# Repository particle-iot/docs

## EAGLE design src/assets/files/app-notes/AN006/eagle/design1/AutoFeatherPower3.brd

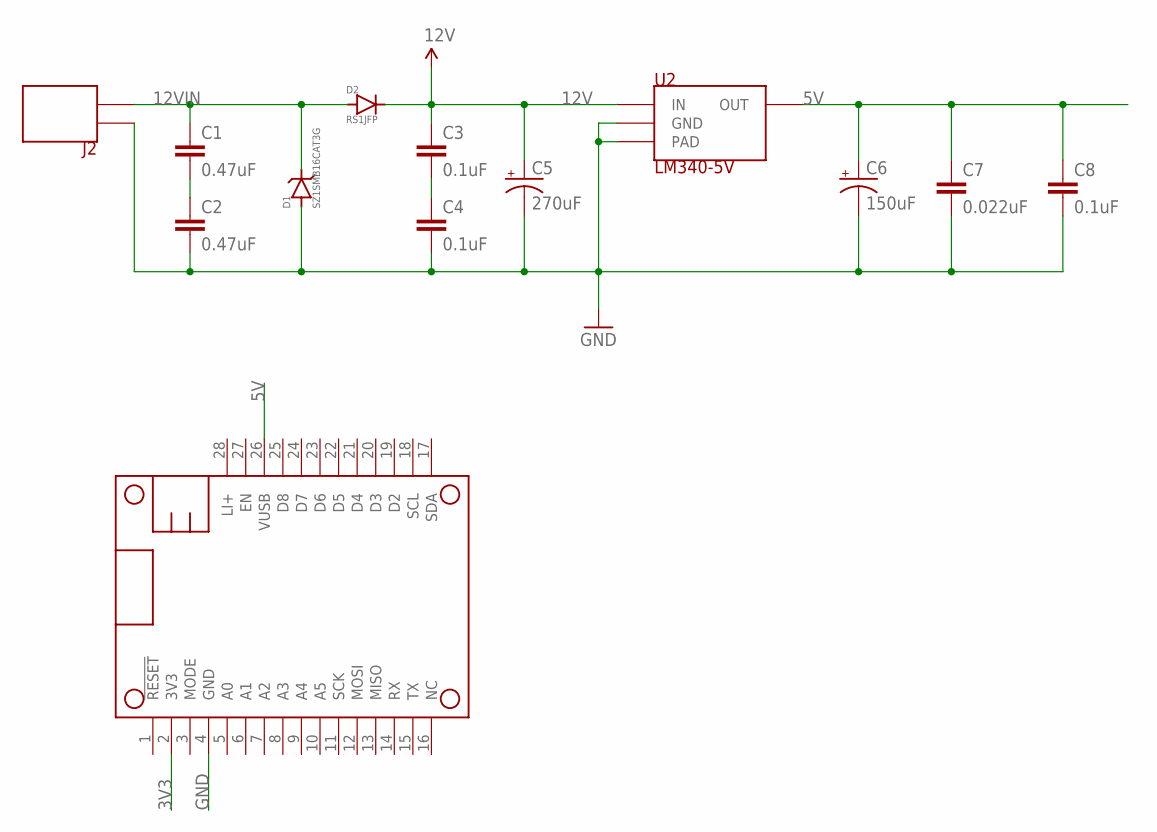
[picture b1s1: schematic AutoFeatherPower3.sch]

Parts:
C1, C2: 0.47uF; 0805
C3, C4, C8: 0.1uF; 0603-CAP
C5: 270uF; CAP-PANASONIC-FKS-V-F
C6: 150uF; CAP-PANASONIC-FKS-V-D
C7: 0.022uF; 0603-CAP
D1: SZ1SMB16CAT3G; SZ1SMB
D2: RS1JFP; SOD-123HE-ON
J2: TERMBLOCK-2X3.5MM
MS1: FEATHERWING_NODIM
U2: LM340-5V; TO-263-3-TI

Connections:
3V3: MS1.2 (3V3)
5V: C6.P+ (+), C7.1, C8.1, MS1.26 (VUSB), U2.3 (OUT)
12V: C3.1, C5.P+ (+), D2.1 (CATHODE), U2.1 (IN)
12VIN: C1.1, D1.C (CATHODE), D2.2 (ANODE), J2.2
GND: C2.2, C4.2, C5.P- (-), C6.P- (-), C7.2, C8.2, D1.A (ANODE), J2.1, MS1.4 (GND), U2.2 (GND), U2.PAD
unnamed: C1.2, C2.1
unnamed: C3.2, C4.1

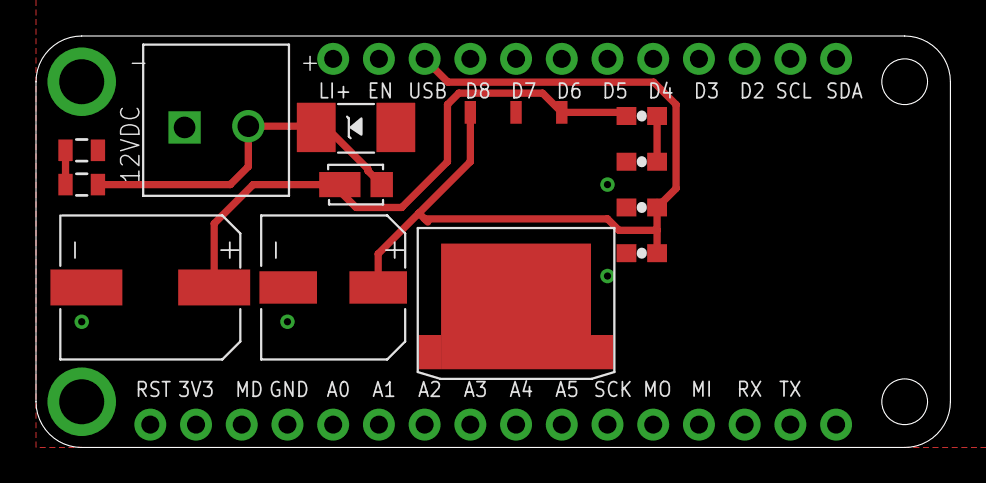
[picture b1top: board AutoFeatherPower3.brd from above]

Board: 2 copper layers, 50.8 x 22.9 mm, 13 parts (0 on the bottom side), 6 nets.

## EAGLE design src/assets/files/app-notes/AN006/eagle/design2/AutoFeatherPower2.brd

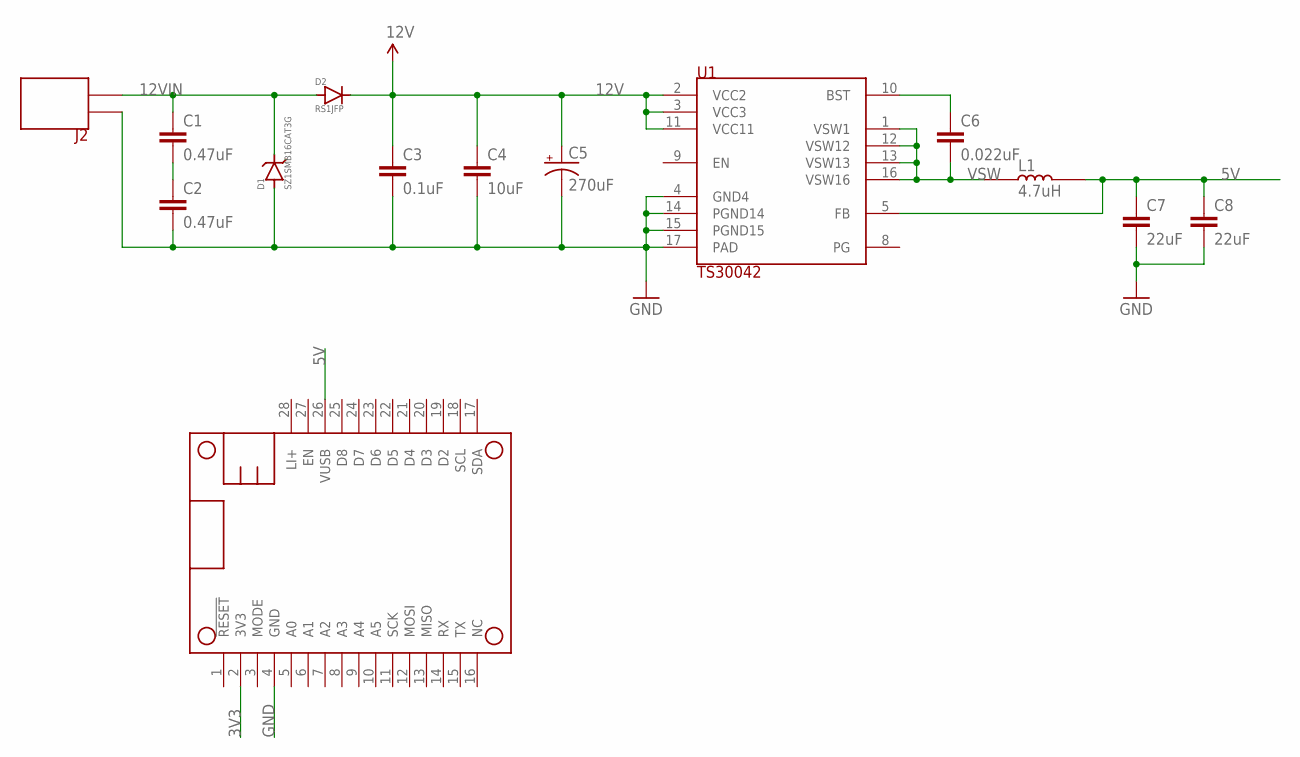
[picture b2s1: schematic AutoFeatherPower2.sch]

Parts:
C1, C2: 0.47uF; 0805
C3: 0.1uF; 0603-CAP
C4: 10uF; 0603-CAP
C5: 270uF; CAP-PANASONIC-FKS-V-F
C6: 0.022uF; 0603-CAP
C7, C8: 22uF; 0805
D1: SZ1SMB16CAT3G; SZ1SMB
D2: RS1JFP; SOD-123HE-ON
J2: TERMBLOCK-2X3.5MM
L1: 4.7uH; WURTH-744774047
MS1: FEATHERWING_NODIM
U1: TS30042; REG-TS30011

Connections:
3V3: MS1.2 (3V3)
5V: C7.1, C8.1, L1.2, MS1.26 (VUSB), U1.5 (FB)
12V: C3.1, C4.1, C5.P+ (+), D2.1 (CATHODE), U1.2 (VCC2), U1.3 (VCC3), U1.11 (VCC11)
12VIN: C1.1, D1.C (CATHODE), D2.2 (ANODE), J2.2
BST: C6.1, U1.10 (BST)
GND: C2.2, C3.2, C4.2, C5.P- (-), C7.2, C8.2, D1.A (ANODE), J2.1, MS1.4 (GND), U1.4 (GND4), U1.14 (PGND14), U1.15 (PGND15), U1.17 (PAD)
unnamed: C1.2, C2.1
VSW: C6.2, L1.1, U1.1 (VSW1), U1.12 (VSW12), U1.13 (VSW13), U1.16 (VSW16)

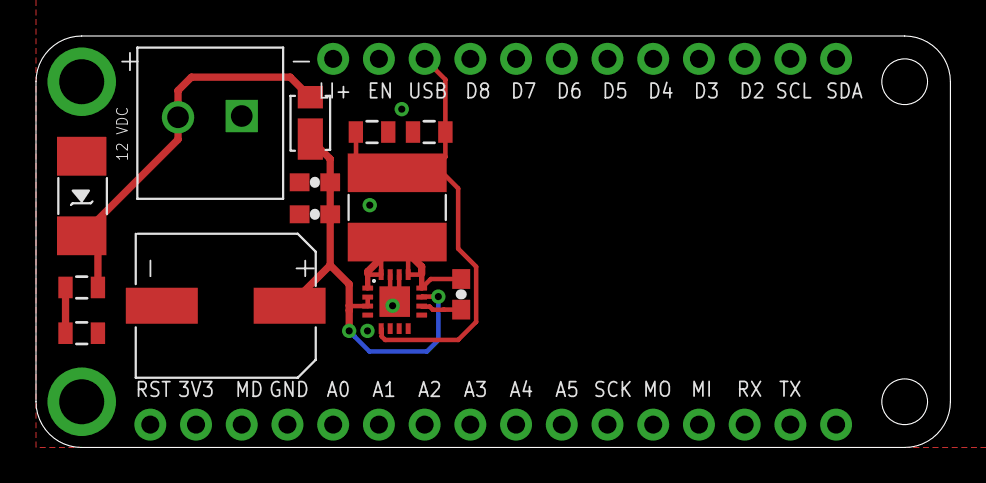
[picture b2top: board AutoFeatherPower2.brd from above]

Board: 2 copper layers, 50.8 x 22.9 mm, 14 parts (0 on the bottom side), 7 nets.

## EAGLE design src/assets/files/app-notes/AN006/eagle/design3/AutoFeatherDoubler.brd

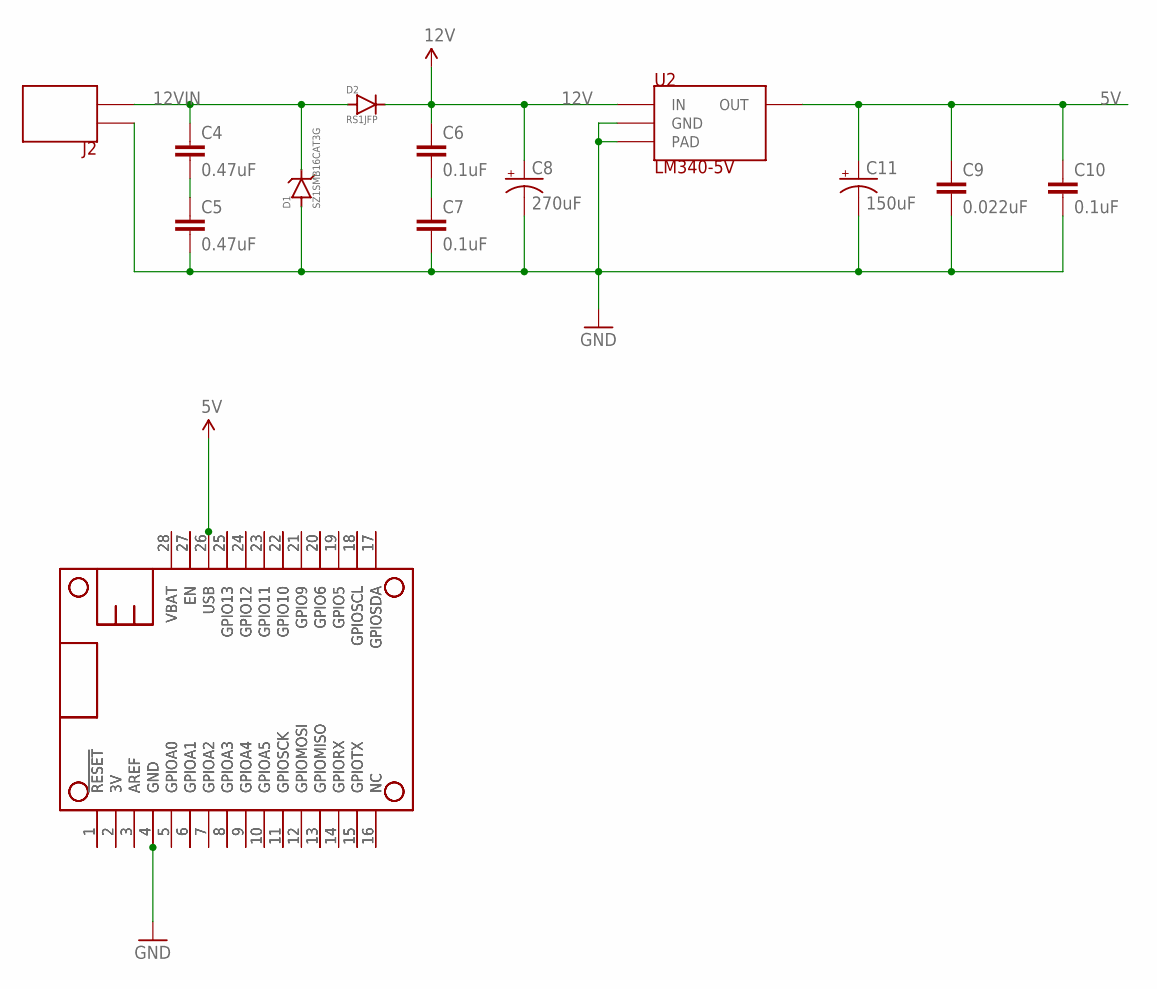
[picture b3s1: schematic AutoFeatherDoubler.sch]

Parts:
C4, C5: 0.47uF; 0805
C6, C7, C10: 0.1uF; 0603-CAP
C8: 270uF; CAP-270UF-25V-RADIAL-PTH
C9: 0.022uF; 0603-CAP
C11: 150uF; CAP-150UF-25V-RADIAL-PTH
D1: SZ1SMB16CAT3G; SZ1SMB
D2: RS1JFP; SOD-123HE-ON
J2: TERMBLOCK-2X3.5MM
MS1, MS2: FEATHERWING_NODIM; FEATHERWING_DIM
U2: LM340-5V; TO-263-3-TI

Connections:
3V3: MS1.2 (3V), MS2.2 (3V)
5V: C9.1, C10.1, C11.+, MS1.26 (USB), MS2.26 (USB), U2.3 (OUT)
12V: C6.1, C8.+, D2.1 (CATHODE), U2.1 (IN)
12VIN: C4.1, D1.C (CATHODE), D2.2 (ANODE), J2.2
A0: MS1.5 (GPIOA0), MS2.5 (GPIOA0)
A1: MS1.6 (GPIOA1), MS2.6 (GPIOA1)
A2: MS1.7 (GPIOA2), MS2.7 (GPIOA2)
A3: MS1.8 (GPIOA3), MS2.8 (GPIOA3)
A4: MS1.9 (GPIOA4), MS2.9 (GPIOA4)
A5: MS1.10 (GPIOA5), MS2.10 (GPIOA5)
D2: MS1.19 (GPIO5), MS2.19 (GPIO5)
D3: MS1.20 (GPIO6), MS2.20 (GPIO6)
D4: MS1.21 (GPIO9), MS2.21 (GPIO9)
D5: MS1.22 (GPIO10), MS2.22 (GPIO10)
D6: MS1.23 (GPIO11), MS2.23 (GPIO11)
D7: MS1.24 (GPIO12), MS2.24 (GPIO12)
D8: MS1.25 (GPIO13), MS2.25 (GPIO13)
EN: MS1.27 (EN), MS2.27 (EN)
GND: C5.2, C7.2, C8.-, C9.2, C10.2, C11.-, D1.A (ANODE), J2.1, MS1.4 (GND), MS2.4 (GND), U2.2 (GND), U2.PAD
MD: MS1.3 (AREF), MS2.3 (AREF)
MISO: MS1.13 (GPIOMISO), MS2.13 (GPIOMISO)
MOSI: MS1.12 (GPIOMOSI), MS2.12 (GPIOMOSI)
unnamed: C4.2, C5.1
unnamed: C6.2, C7.1
NC: MS1.16 (NC), MS2.16 (NC)
RESET: MS1.1 (!RESET), MS2.1 (!RESET)
RX: MS1.14 (GPIORX), MS2.14 (GPIORX)
SCK: MS1.11 (GPIOSCK), MS2.11 (GPIOSCK)
SCL: MS1.18 (GPIOSCL), MS2.18 (GPIOSCL)
SDA: MS1.17 (GPIOSDA), MS2.17 (GPIOSDA)
TX: MS1.15 (GPIOTX), MS2.15 (GPIOTX)
VBAT: MS1.28 (VBAT), MS2.28 (VBAT)

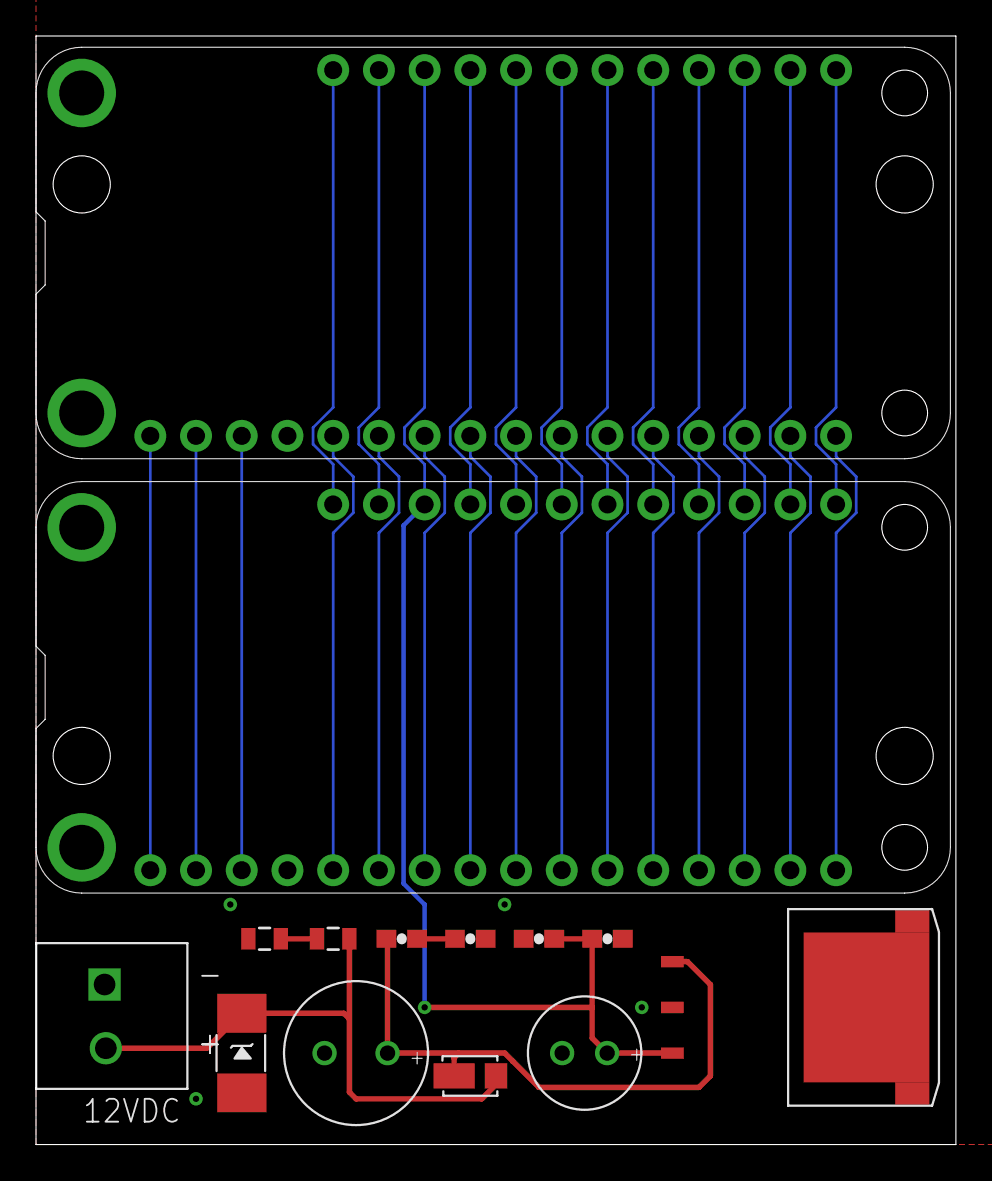
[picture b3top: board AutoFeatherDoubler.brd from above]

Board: 2 copper layers, 51.1 x 61.6 mm, 14 parts (0 on the bottom side), 32 nets.

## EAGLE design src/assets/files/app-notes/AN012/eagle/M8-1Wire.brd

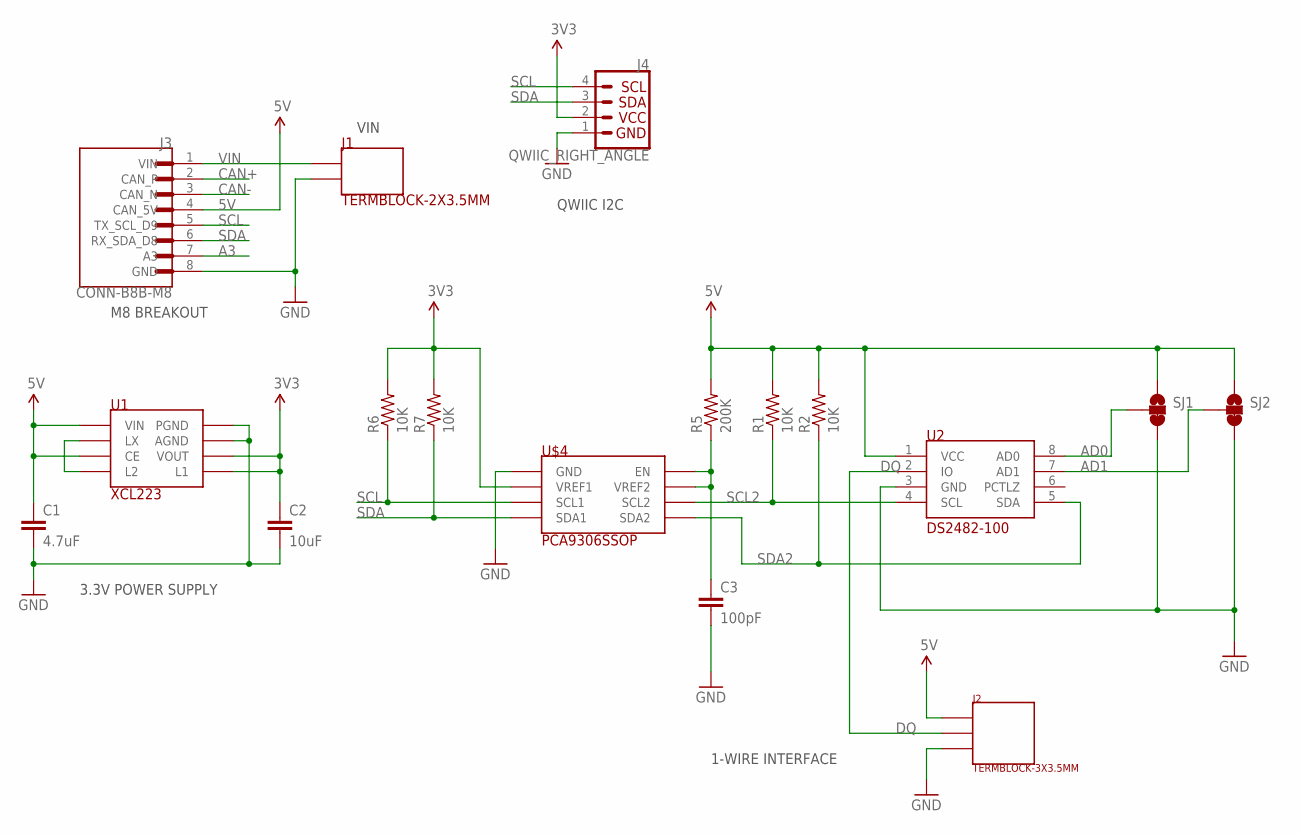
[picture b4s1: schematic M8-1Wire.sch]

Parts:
C1: 4.7uF; 0603-CAP
C2: 10uF; 0603-CAP
C3: 100pF; 0603-CAP
J1: TERMBLOCK-2X3.5MM
J2: TERMBLOCK-3X3.5MM
J3: CONN-B8B-M8; JST_B8B-PH-SM4-TB(LF)(SN)
J4: QWIIC_RIGHT_ANGLE; JST04_1MM_RA
R1, R2, R6, R7: 10K; 0603-RES
R5: 200K; 0603-RES
SJ1, SJ2: JUMPER-PAD-3-2OF3_NC_BY_TRACE_SMALL; PAD-JUMPER-3-2OF3_NC_BY_TRACE_NO_SILK
U1: XCL223; REG-XCL223-LESS-CREAM
U2: DS2482-100; 8-SOIC-MAXIM
U$4: PCA9306SSOP; 8-SSOP-TI

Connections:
3V3: C2.1, J4.2, R6.2, R7.2, U1.3 (VOUT), U1.7 (L1), U$4.2 (VREF1)
5V: C1.1, J2.1, J3.4 (CAN_5V), R1.2, R2.2, R5.2, SJ1.1, SJ2.1, U1.4 (CE), U1.6 (VIN), U2.1 (VCC)
A3: J3.7 (A3)
AD0: SJ1.2, U2.8 (AD0)
AD1: SJ2.2, U2.7 (AD1)
CAN+: J3.2 (CAN_P)
CAN-: J3.3 (CAN_N)
DQ: J2.2, U2.2 (IO)
GND: C1.2, C2.2, C3.2, J1.2, J2.3, J3.8 (GND), J4.1, SJ1.3, SJ2.3, U1.1 (PGND), U1.2 (AGND), U2.3 (GND), U$4.1 (GND)
LX: U1.5 (LX), U1.8 (L2)
SCL: J3.5 (TX_SCL_D9), J4.4, R6.1, U$4.3 (SCL1)
SCL2: R1.1, U2.4 (SCL), U$4.6 (SCL2)
SDA: J3.6 (RX_SDA_D8), J4.3, R7.1, U$4.4 (SDA1)
SDA2: R2.1, U2.5 (SDA), U$4.5 (SDA2)
VIN: J1.1, J3.1 (VIN)
VREF2_EN: C3.1, R5.1, U$4.7 (VREF2), U$4.8 (EN)

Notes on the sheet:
3.3V POWER SUPPLY
QWIIC I2C
M8 BREAKOUT
VIN
1-WIRE INTERFACE

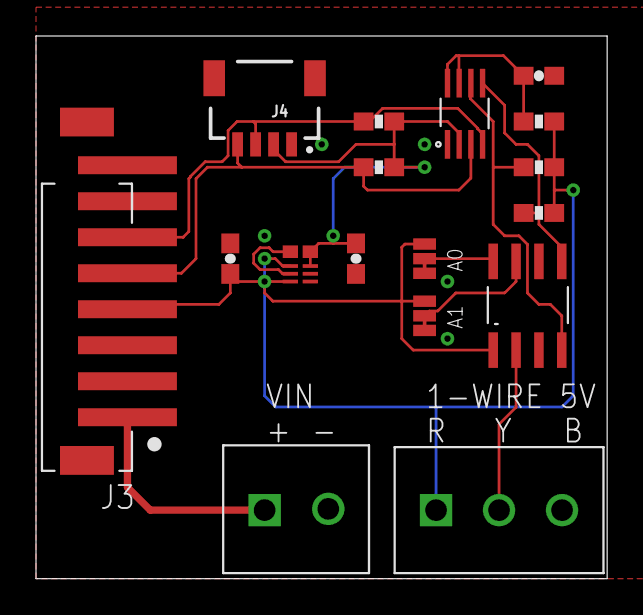
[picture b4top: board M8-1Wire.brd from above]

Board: 2 copper layers, 31.7 x 30.1 mm, 17 parts (0 on the bottom side), 13 nets.

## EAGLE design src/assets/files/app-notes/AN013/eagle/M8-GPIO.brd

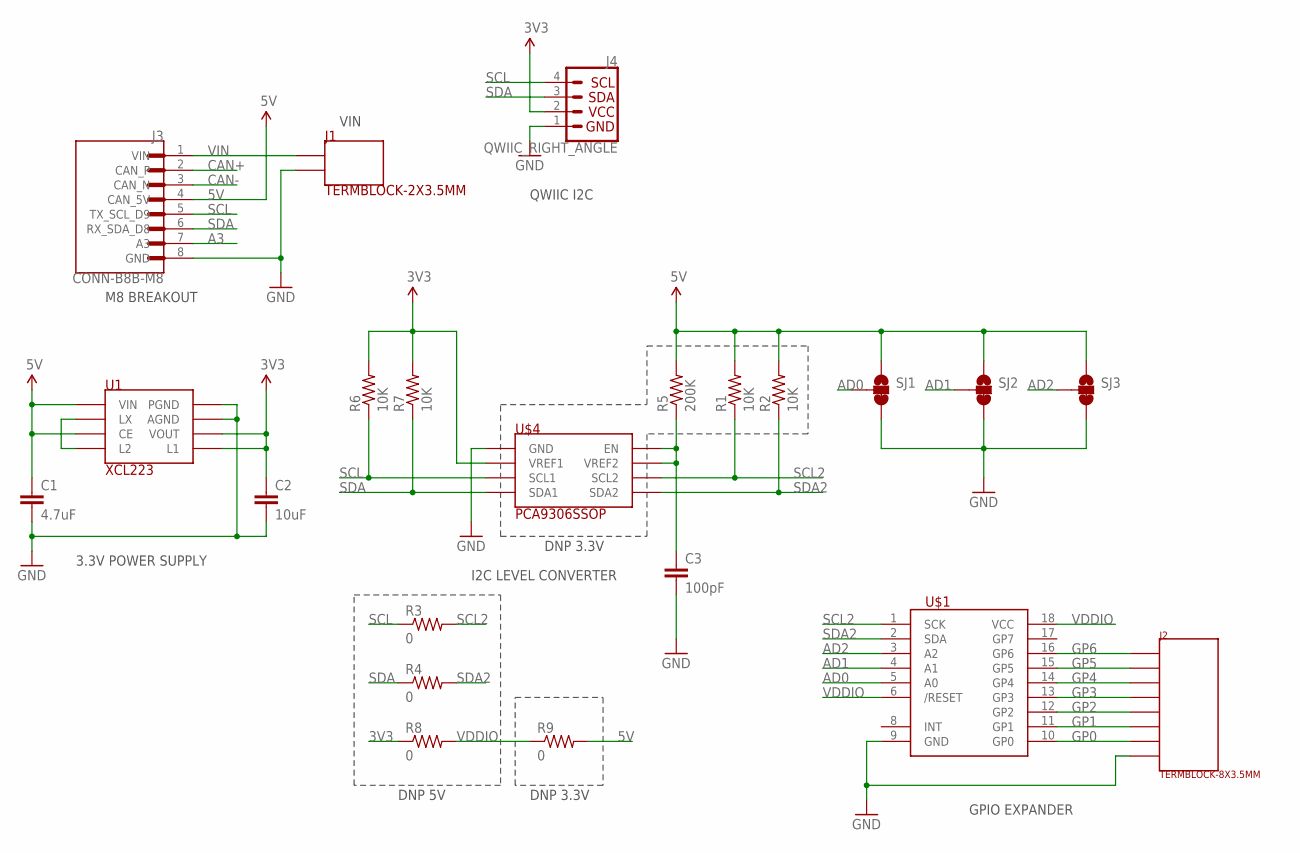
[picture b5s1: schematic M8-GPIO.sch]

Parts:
C1: 4.7uF; 0603-CAP
C2: 10uF; 0603-CAP
C3: 100pF; 0603-CAP
J1: TERMBLOCK-2X3.5MM
J2: TERMBLOCK-8X3.5MM
J3: CONN-B8B-M8; JST_B8B-PH-SM4-TB(LF)(SN)
J4: QWIIC_RIGHT_ANGLE; JST04_1MM_RA
R1, R2, R6, R7: 10K; 0603-RES
R3, R4, R8, R9: 0; 0603-RES
R5: 200K; 0603-RES
SJ1, SJ2, SJ3: JUMPER-PAD-3-2OF3_NC_BY_TRACE_SMALL; PAD-JUMPER-3-2OF3_NC_BY_TRACE_NO_SILK
U1: XCL223; REG-XCL223-LESS-CREAM
U$1: MCP23008; SOIC-18-W-MAXIM
U$4: PCA9306SSOP; 8-SSOP-TI

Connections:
3V3: C2.1, J4.2, R6.2, R7.2, R8.1, U1.3 (VOUT), U1.7 (L1), U$4.2 (VREF1)
5V: C1.1, J3.4 (CAN_5V), R1.2, R2.2, R5.2, R9.2, SJ1.1, SJ2.1, SJ3.1, U1.4 (CE), U1.6 (VIN)
A3: J3.7 (A3)
AD0: SJ1.2, U$1.5 (A0)
AD1: SJ2.2, U$1.4 (A1)
AD2: SJ3.2, U$1.3 (A2)
CAN+: J3.2 (CAN_P)
CAN-: J3.3 (CAN_N)
GND: C1.2, C2.2, C3.2, J1.2, J2.8, J3.8 (GND), J4.1, SJ1.3, SJ2.3, SJ3.3, U1.1 (PGND), U1.2 (AGND), U$1.9 (GND), U$4.1 (GND)
GP0: J2.7, U$1.10 (GP0)
GP1: J2.6, U$1.11 (GP1)
GP2: J2.5, U$1.12 (GP2)
GP3: J2.4, U$1.13 (GP3)
GP4: J2.3, U$1.14 (GP4)
GP5: J2.2, U$1.15 (GP5)
GP6: J2.1, U$1.16 (GP6)
LX: U1.5 (LX), U1.8 (L2)
SCL: J3.5 (TX_SCL_D9), J4.4, R3.1, R6.1, U$4.3 (SCL1)
SCL2: R1.1, R3.2, U$1.1 (SCK), U$4.6 (SCL2)
SDA: J3.6 (RX_SDA_D8), J4.3, R4.1, R7.1, U$4.4 (SDA1)
SDA2: R2.1, R4.2, U$1.2 (SDA), U$4.5 (SDA2)
VDDIO: R8.2, R9.1, U$1.6 (/RESET), U$1.18 (VCC)
VIN: J1.1, J3.1 (VIN)
VREF2_EN: C3.1, R5.1, U$4.7 (VREF2), U$4.8 (EN)

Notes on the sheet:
3.3V POWER SUPPLY
QWIIC I2C
M8 BREAKOUT
VIN
DNP 3.3V
DNP 5V
GPIO EXPANDER
I2C LEVEL CONVERTER

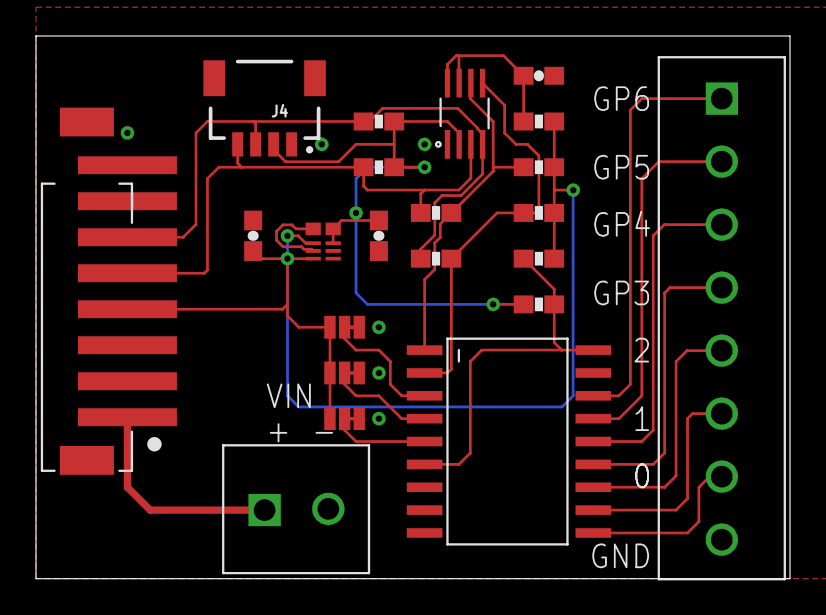
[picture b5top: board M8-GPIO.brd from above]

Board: 2 copper layers, 41.9 x 30.1 mm, 22 parts (0 on the bottom side), 21 nets.

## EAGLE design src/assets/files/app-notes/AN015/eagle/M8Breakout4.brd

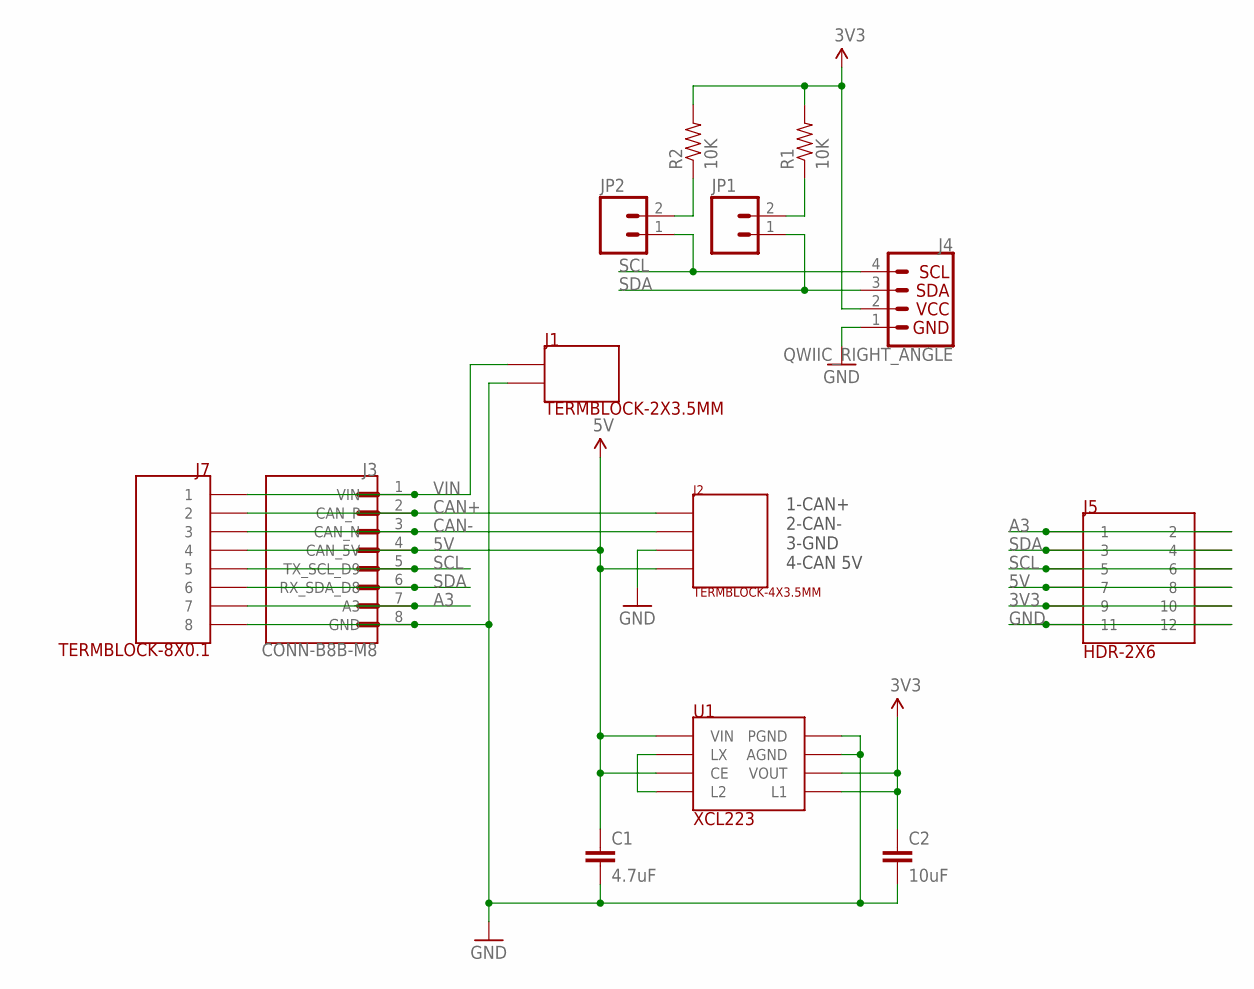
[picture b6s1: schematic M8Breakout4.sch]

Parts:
C1: 4.7uF; 0603-CAP
C2: 10uF; 0603-CAP
J1: TERMBLOCK-2X3.5MM
J2: TERMBLOCK-4X3.5MM
J3: CONN-B8B-M8; JST_B8B-PH-SM4-TB(LF)(SN)
J4: QWIIC_RIGHT_ANGLE; JST04_1MM_RA
J5: HDR-2X6; HDR-2X6-F-SMD-NO-HOLES
J7: TERMBLOCK-8X0.1
JP1, JP2: M02PTH; 1X02
R1, R2: 10K; 0603-RES
U1: XCL223; REG-XCL223-LESS-CREAM

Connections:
3V3: C2.1, J4.2, J5.9, J5.10, R1.2, R2.2, U1.3 (VOUT), U1.7 (L1)
5V: C1.1, J2.4, J3.4 (CAN_5V), J5.7, J5.8, J7.P$4 (4), U1.4 (CE), U1.6 (VIN)
A3: J3.7 (A3), J5.1, J5.2, J7.P$7 (7)
CAN+: J2.1, J3.2 (CAN_P), J7.P$2 (2)
CAN-: J2.2, J3.3 (CAN_N), J7.P$3 (3)
GND: C1.2, C2.2, J1.2, J2.3, J3.8 (GND), J4.1, J5.11, J5.12, J7.P$8 (8), U1.1 (PGND), U1.2 (AGND)
LX: U1.5 (LX), U1.8 (L2)
unnamed: JP2.2, R2.1
unnamed: JP1.2, R1.1
SCL: J3.5 (TX_SCL_D9), J4.4, J5.5, J5.6, J7.P$5 (5), JP2.1
SDA: J3.6 (RX_SDA_D8), J4.3, J5.3, J5.4, J7.P$6 (6), JP1.1
VIN: J1.1, J3.1 (VIN), J7.P$1 (1)

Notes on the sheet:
1-CAN+ 2-CAN- 3-GND 4-CAN 5V

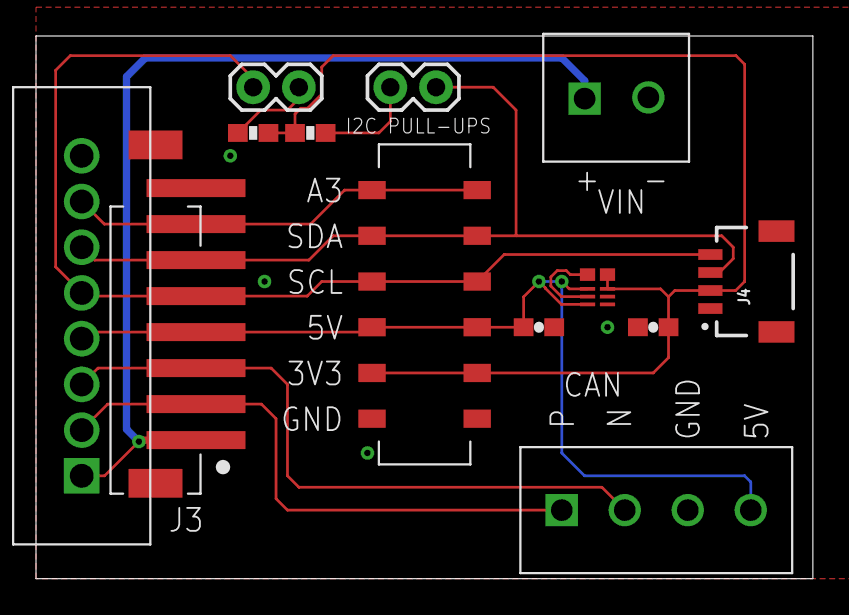
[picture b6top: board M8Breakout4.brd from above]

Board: 2 copper layers, 43.2 x 30.1 mm, 13 parts (0 on the bottom side), 12 nets.

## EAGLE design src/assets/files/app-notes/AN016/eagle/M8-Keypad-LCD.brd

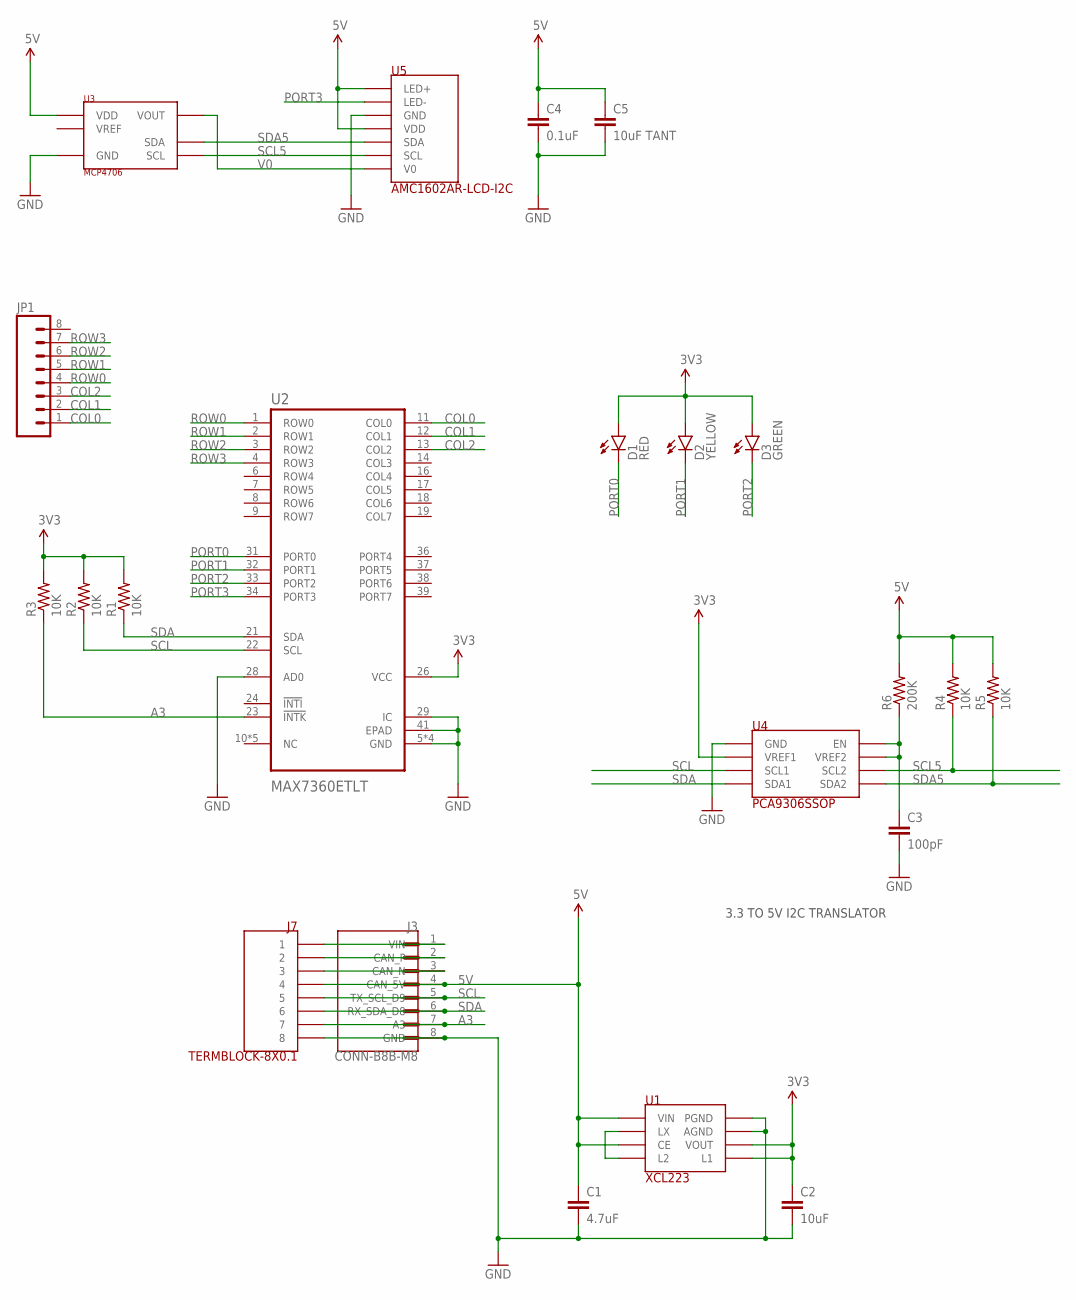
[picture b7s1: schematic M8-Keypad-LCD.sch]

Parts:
C1: 4.7uF; 0603-CAP
C2: 10uF; 0603-CAP
C3: 100pF; 0603-CAP
C4: 0.1uF; 0603-CAP
C5: 10uF TANT; 1206-KEMET
D1: RED; LED-0603
D2: YELLOW; LED-0603
D3: GREEN; LED-0603
J3: CONN-B8B-M8; JST_B8B-PH-SM4-TB(LF)(SN)
J7: TERMBLOCK-8X0.1
JP1: M08SILK_FEMALE_PTH; 1X08
R1, R2, R3, R4, R5: 10K; 0603-RES
R6: 200K; 0603-RES
U1: XCL223; REG-XCL223-LESS-CREAM
U2: MAX7360ETLT; QFN40P500X500X80-41N
U3: MCP4706; SOT-23-6-MICROCHIP
U4: PCA9306SSOP; 8-SSOP-TI
U5: AMC1602AR-LCD-I2C; AMC1602AR

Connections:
3V3: C2.1, D1.A, D2.A, D3.A, R1.2, R2.2, R3.2, U1.3 (VOUT), U1.7 (L1), U2.26 (VCC), U4.2 (VREF1)
5V: C1.1, C4.1, C5.1, J3.4 (CAN_5V), J7.P$4 (4), R4.2, R5.2, R6.2, U1.4 (CE), U1.6 (VIN), U3.3 (VDD), U5.1 (LED+), U5.4 (VDD)
A3: J3.7 (A3), J7.P$7 (7), R3.1, U2.23 (!INTK)
CAN+: J3.2 (CAN_P), J7.P$2 (2)
CAN-: J3.3 (CAN_N), J7.P$3 (3)
COL0: JP1.1, U2.11 (COL0)
COL1: JP1.2, U2.12 (COL1)
COL2: JP1.3, U2.13 (COL2)
GND: C1.2, C2.2, C3.2, C4.2, C5.2, J3.8 (GND), J7.P$8 (8), U1.1 (PGND), U1.2 (AGND), U2.5 (GND), U2.15 (GND), U2.25 (GND), U2.28 (AD0), U2.29 (IC), U2.35 (GND), U2.41 (EPAD), U3.2 (GND), U4.1 (GND), U5.3 (GND)
LX: U1.5 (LX), U1.8 (L2)
PORT0: D1.C, U2.31 (PORT0)
PORT1: D2.C, U2.32 (PORT1)
PORT2: D3.C, U2.33 (PORT2)
PORT3: U2.34 (PORT3), U5.2 (LED-)
ROW0: JP1.4, U2.1 (ROW0)
ROW1: JP1.5, U2.2 (ROW1)
ROW2: JP1.6, U2.3 (ROW2)
ROW3: JP1.7, U2.4 (ROW3)
SCL: J3.5 (TX_SCL_D9), J7.P$5 (5), R2.1, U2.22 (SCL), U4.3 (SCL1)
SCL5: R4.1, U3.5 (SCL), U4.6 (SCL2), U5.6 (SCL)
SDA: J3.6 (RX_SDA_D8), J7.P$6 (6), R1.1, U2.21 (SDA), U4.4 (SDA1)
SDA5: R5.1, U3.4 (SDA), U4.5 (SDA2), U5.5 (SDA)
V0: U3.1 (VOUT), U5.7 (V0)
VIN: J3.1 (VIN), J7.P$1 (1)
VREF2_EN: C3.1, R6.1, U4.7 (VREF2), U4.8 (EN)

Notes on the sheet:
3.3 TO 5V I2C TRANSLATOR

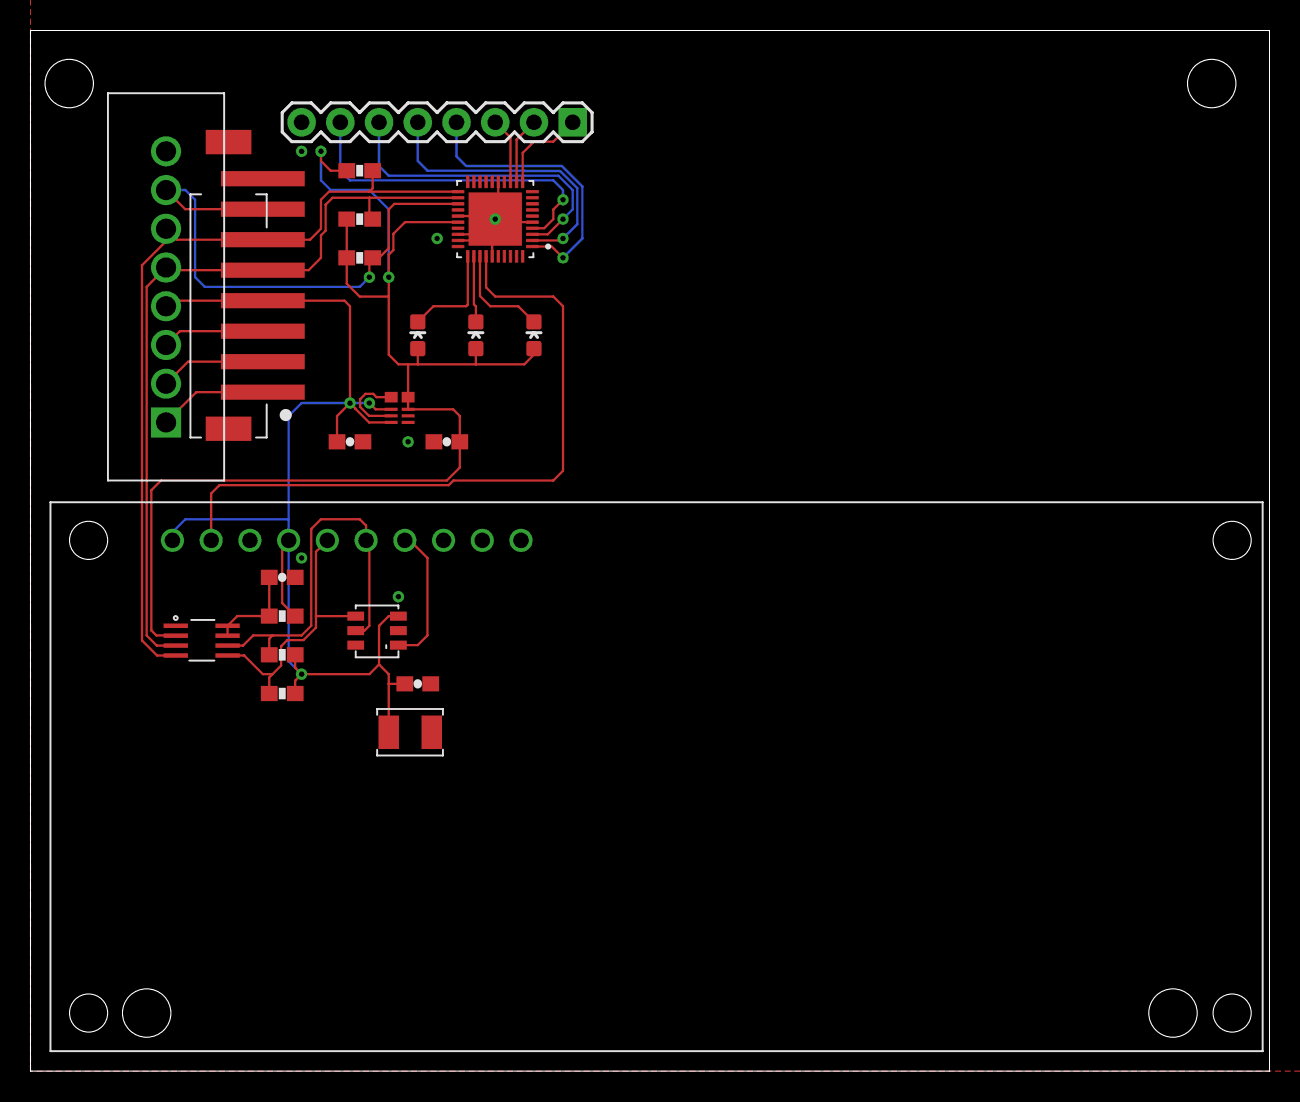
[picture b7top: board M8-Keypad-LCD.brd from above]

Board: 2 copper layers, 81.3 x 68.2 mm, 22 parts (0 on the bottom side), 25 nets.

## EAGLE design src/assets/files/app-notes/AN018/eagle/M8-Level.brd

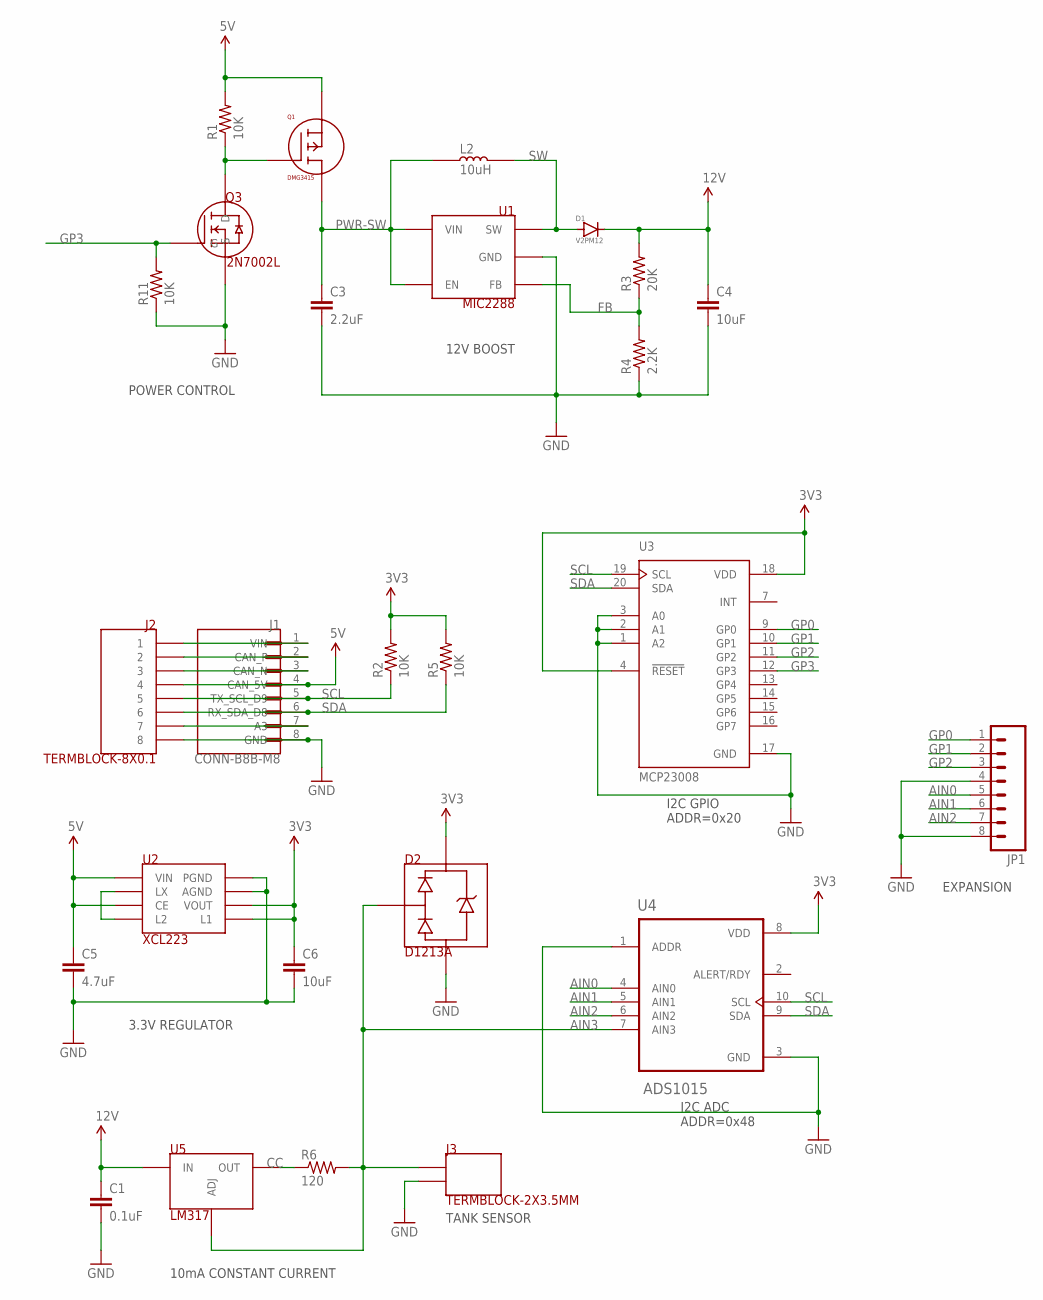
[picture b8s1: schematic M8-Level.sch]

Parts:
C1: 0.1uF; 0603-CAP
C3: 2.2uF; 0603-CAP
C4, C6: 10uF; 0603-CAP
C5: 4.7uF; 0603-CAP
D1: V2PM12; DO-219AD-VISHAY
D2: D1213A; DLP
J1: CONN-B8B-M8; JST_B8B-PH-SM4-TB(LF)(SN)
J2: TERMBLOCK-8X0.1
J3: TERMBLOCK-2X3.5MM
JP1: M08SILK_FEMALE_PTH; 1X08
L2: 10uH; BOURNS-INDUCTOR-3X3
Q1: DMG3415; 2N7002L
Q3: 2N7002L
R1, R2, R5, R11: 10K; 0603-RES
R3: 20K; 0603-RES
R4: 2.2K; 0603-RES
R6: 120; 0603-RES
U1: MIC2288; TSOT23-5-MICROCHIP
U2: XCL223; REG-XCL223-LESS-CREAM
U3: MCP23008; QFN21P50_400X400X100L40X24T270N
U4: ADS1015; SOP50P490X110-10N
U5: LM317; 8-SOIC-ON751

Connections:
3V3: C6.1, D2.VCC, R2.2, R5.2, U2.3 (VOUT), U2.7 (L1), U3.4 (!RESET), U3.18 (VDD), U4.8 (VDD)
5V: C5.1, J1.4 (CAN_5V), J2.P$4 (4), Q1.2 (S), R1.2, U2.4 (CE), U2.6 (VIN)
12V: C1.1, C4.1, D1.C (CATHODE), R3.2, U5.1 (IN)
A3: J1.7 (A3), J2.P$7 (7)
AIN0: JP1.5, U4.4 (AIN0)
AIN1: JP1.6, U4.5 (AIN1)
AIN2: JP1.7, U4.6 (AIN2)
AIN3: D2.SIGNAL, J3.1, R6.2, U4.7 (AIN3), U5.4 (ADJ)
CAN_N: J1.3 (CAN_N), J2.P$3 (3)
CAN_P: J1.2 (CAN_P), J2.P$2 (2)
CC: R6.1, U5.2 (OUT), U5.3 (OUT), U5.6 (OUT), U5.7 (OUT)
FB: R3.1, R4.2, U1.3 (FB)
GND: C1.2, C3.2, C4.2, C5.2, C6.2, D2.GND, J1.8 (GND), J2.P$8 (8), J3.2, JP1.4, JP1.8, Q3.2 (S), R4.1, R11.1, U1.2 (GND), U2.1 (PGND), U2.2 (AGND), U3.1 (A2), U3.2 (A1), U3.3 (A0), U3.17 (GND), U4.1 (ADDR), U4.3 (GND)
GP0: JP1.1, U3.9 (GP0)
GP1: JP1.2, U3.10 (GP1)
GP2: JP1.3, U3.11 (GP2)
GP3: Q3.1 (G), R11.2, U3.12 (GP3)
LX1: U2.5 (LX), U2.8 (L2)
PWR-SW: C3.1, L2.1, Q1.3 (D), U1.4 (EN), U1.5 (VIN)
PWRCTL: Q1.1 (G), Q3.3 (D), R1.1
SCL: J1.5 (TX_SCL_D9), J2.P$5 (5), R2.1, U3.19 (SCL), U4.10 (SCL)
SDA: J1.6 (RX_SDA_D8), J2.P$6 (6), R5.1, U3.20 (SDA), U4.9 (SDA)
SW: D1.A (ANODE), L2.2, U1.1 (SW)
VIN: J1.1 (VIN), J2.P$1 (1)

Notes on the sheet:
3.3V REGULATOR
12V BOOST
10mA CONSTANT CURRENT
TANK SENSOR
I2C ADC ADDR=0x48
I2C GPIO ADDR=0x20
EXPANSION
POWER CONTROL

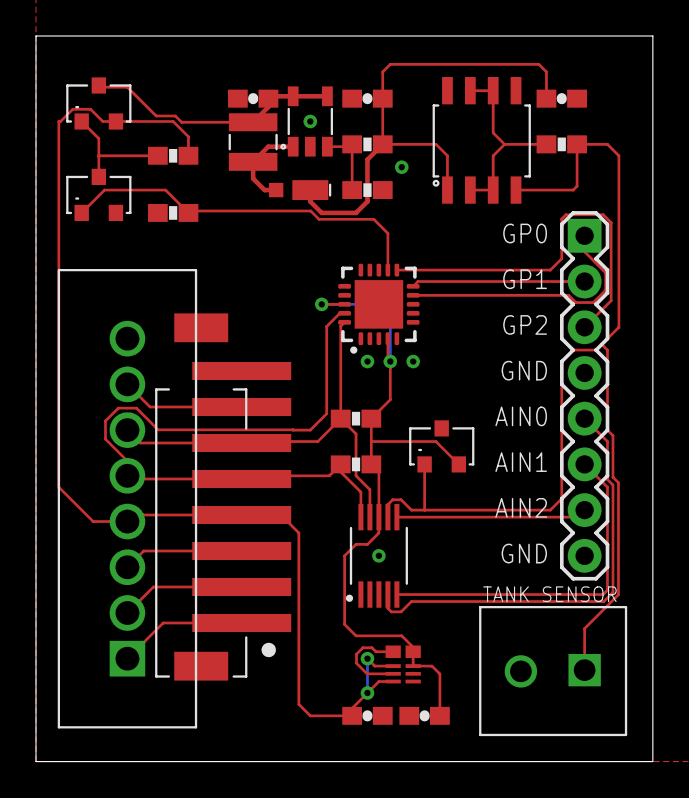
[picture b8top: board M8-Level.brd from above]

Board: 2 copper layers, 34.3 x 40.3 mm, 26 parts (0 on the bottom side), 24 nets.
